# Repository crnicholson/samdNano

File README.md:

# samdNano+

The samdNano+ is based on the Arduino Nano board. The format was extended to allow for more pins to be broken out. It uses the powerful SAMD21G18A chip that is significantly faster and more powerful than the Arduino Nano. It boasts extra pins just for SPI and I2C, while additionally the option to disable LEDs and the power regulator for ultra-low power performance. 

# License

samdNano+ is licensed under the CERN Open Hardware Licence Version 2 - Strongly Reciprocal to allow to modify it and make their own.

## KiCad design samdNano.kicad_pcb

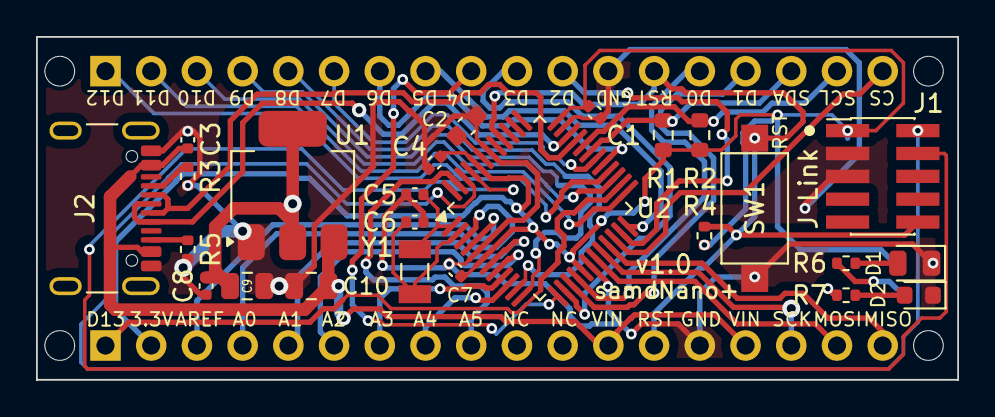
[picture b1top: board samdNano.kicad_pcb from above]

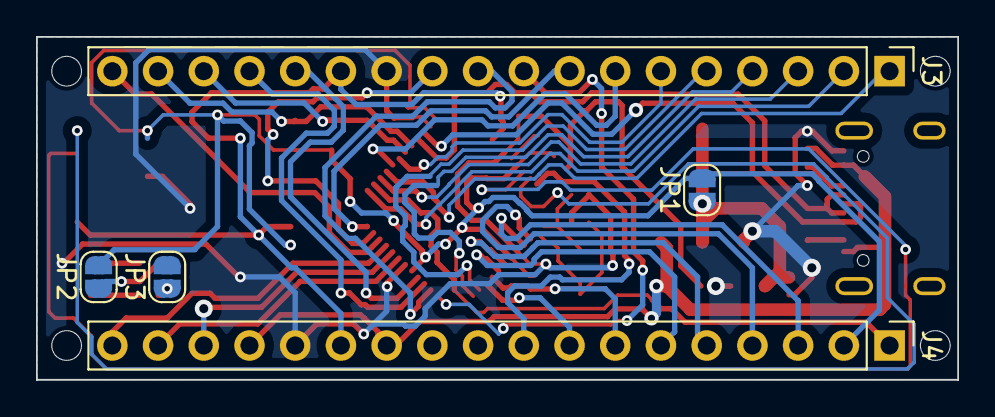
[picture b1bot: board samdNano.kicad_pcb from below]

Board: 2 copper layers, 51.2 x 19.1 mm, 34 parts (5 on the bottom side), 45 nets.

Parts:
C1, C3, C4, C7, C8: 100 nF; C_0402_1005Metric
C2: 1 uF; C_0603_1608Metric
C5, C6: 22 pF; C_0402_1005Metric
C9, C10: 10 uF; C_0805_2012Metric
D1: PWR_LED; LED_0805_2012Metric
D2: LED; LED_0603_1608Metric
J1: J Link; PinHeader_2x05_P1.27mm_Vertical_SMD
J2: USB-C; USB_C_Receptacle_GCT_USB4105-xx-A_16P_TopMnt_Horizontal
J3: Digital; PinHeader_1x18_P2.54mm_Vertical
J4: Analog; PinHeader_1x18_P2.54mm_Vertical
JP1: PWR_EN; SolderJumper-2_P1.3mm_Open_RoundedPad1.0x1.5mm
JP2: PWR_LED_EN; SolderJumper-2_P1.3mm_Open_RoundedPad1.0x1.5mm
JP3: LED_EN; SolderJumper-2_P1.3mm_Open_RoundedPad1.0x1.5mm
MH1, MH2, MH3, MH4: MountingHole_65mil
R1, R2: 1.8 K; R_0603_1608Metric
R3, R5: 5.1 K; R_0402_1005Metric
R4: 220; R_0402_1005Metric
R6, R7: 1 K; R_0402_1005Metric
SW1: RESET; SW_SPST_CK_RS282G05A3
U1: AMS1117-3.3; SOT-223-3_TabPin2
U2: ATSAMD21G18A-A; TQFP-48_7x7mm_P0.5mm
Y1: 32.768 kHz; XTAL_CM7V-T1A-32.768K-12.5PF-20PPM-TA-QA

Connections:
+3.3V: C1.1, C4.2, C7.1, J1.1, J4.2, JP1.2 (B), JP2.2 (B), R1.2, R2.2, R4.1, U2.6 (VDDANA), U2.17 (VDDIO), U2.36 (VDDIO), U2.44 (VDDIN)
+5V: C3.1, C10.1, J2.A4 (VBUS), J2.A9 (VBUS), J2.B4 (VBUS), J2.B9 (VBUS), J4.12, J4.15, U1.3 (VI)
A0: J4.4, U2.3 (PA02)
A1: J4.5, U2.7 (PB08)
A2: J4.6, U2.8 (PB09)
A3: J4.7, U2.9 (PA04)
A4: J4.8, U2.10 (PA05)
A5: J4.9, U2.47 (PB02)
AREF: J4.3, U2.4 (PA03)
CS: J3.18, U2.22 (PA13)
D0: J3.14, U2.16 (PA11)
D1: J3.15, U2.15 (PA10)
D2: J3.11, U2.23 (PA14)
D3: J3.10, U2.14 (PA09)
D4: J3.9, U2.13 (PA08)
D5: J3.8, U2.24 (PA15)
D6: J3.7, U2.29 (PA20)
D7: J3.6, U2.30 (PA21)
D8: J3.5, U2.11 (PA06)
D9: J3.4, U2.12 (PA07)
D10: J3.3, U2.27 (PA18)
D11: J3.2, U2.25 (PA16)
D12: J3.1, U2.28 (PA19)
D13: J4.1, U2.26 (PA17)
D+: J2.A6 (D+), J2.B6 (D+), U2.34 (PA25)
D-: J2.A7 (D-), J2.B7 (D-), U2.33 (PA24)
GND: C1.2, C2.2, C3.2, C4.1, C5.2, C6.2, C7.2, C8.2, C9.2, C10.2, D1.1 (K), D2.1 (K), J1.3, J1.5, J2.A1 (GND), J2.A12 (GND), J2.B1 (GND), J2.B12 (GND), J3.12, J4.14, R3.2, R5.2, SW1.1, U1.1 (GND), U2.5 (GNDANA), U2.18 (GND), U2.35 (GND), U2.42 (GND)
MISO: J4.18, U2.21 (PA12)
MOSI: J4.17, U2.19 (PB10)
unnamed: D2.2 (A), R7.1
unnamed: D1.2 (A), R6.1
unnamed: J2.A5 (CC1), R3.1
unnamed: J2.B5 (CC2), R5.1
unnamed: C8.1, C9.1, JP1.1 (A), U1.2 (VO)
unnamed: JP3.1 (A), R7.2
unnamed: JP2.1 (A), R6.2
unnamed: C2.1, U2.43 (VDDCORE)
RST: J1.10, J3.13, J4.13, R4.2, SW1.2, U2.40 (~RESET)
SCK: J4.16, U2.20 (PB11)
SCL: J3.17, R2.1, U2.32 (PA23)
SDA: J3.16, R1.1, U2.31 (PA22)
SWCLK: J1.4, U2.45 (PA30)
SWDIO: J1.2, U2.46 (PA31)
XIN: C5.1, U2.1 (PA00), Y1.1
XOUT: C6.1, U2.2 (PA01), Y1.2

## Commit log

2024-06-24 Footprints
2024-06-24 Basic layout
2024-06-25 routing
2024-06-27 Almost finished!!!!
2024-06-27 almost finished board
2024-07-07 Finished board and silkscreen
2024-07-07 Cleaning up the repo
2024-07-07 Stop tracking files now in .gitignore
